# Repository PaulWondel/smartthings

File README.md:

# THIS PROJECT HAS BEEN FINALIZED AND SHELVED

# Minor Smart Things

This github is for all the files I create or save during the minor `Smart Things` that I
follow at the [Rotterdam University of Applied Sciences](https://rotterdamuas.com/) - Applied Computer Science
([Hogeschool Rotterdam](https://www.hogeschoolrotterdam.nl/) - Technische Informatica).

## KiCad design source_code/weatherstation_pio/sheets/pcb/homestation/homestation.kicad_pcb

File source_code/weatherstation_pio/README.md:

# Weather Station with ESP8266

## Libraries
Required library from RicArch97: https://github.com/RicArch97/ESP-smart-things.

## Important note
To use the ssid and password you will need to create your own `credentials.h` headerfile using
the `credentials_example.h`. You can simply just copy it.  
To upload the data to your own website edit the information in the `httpclient.h` file.

## Design
Here are the designs on how the circuit and system is built.

### Fritzing

### Electrical Scheme

### Software Architecture

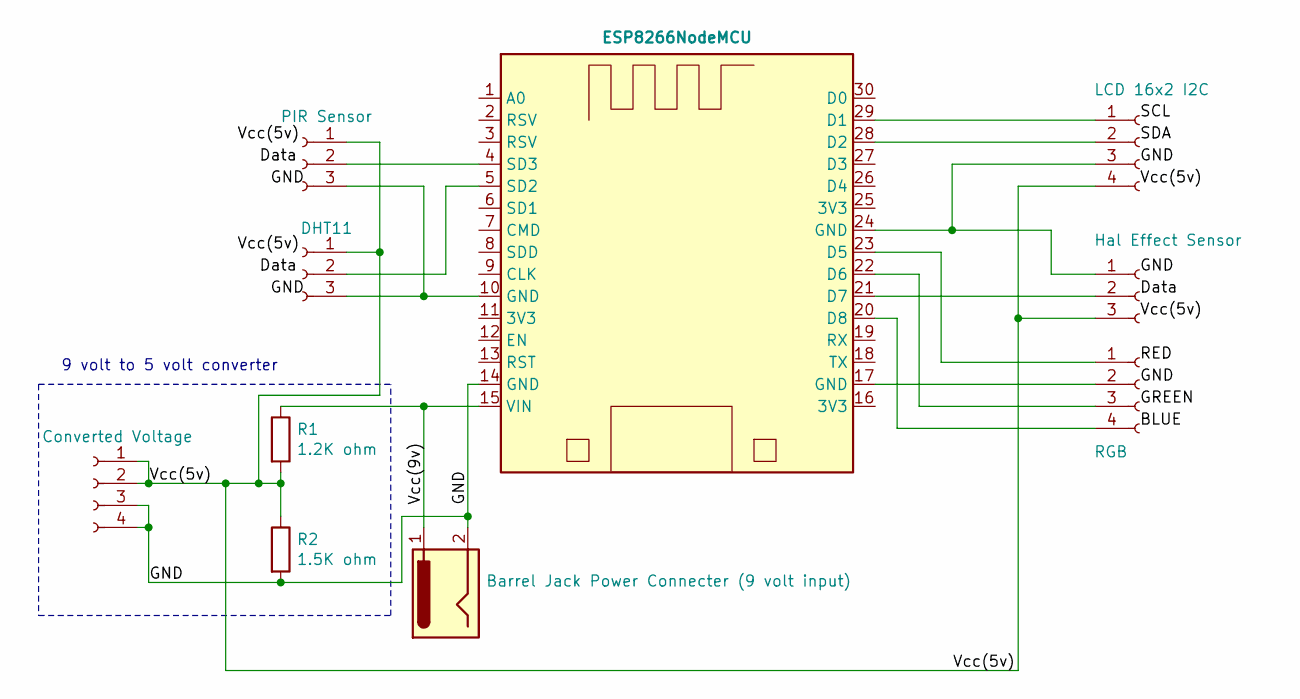
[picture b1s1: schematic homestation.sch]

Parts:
J1: Converted Voltage; PinHeader_1x04_P2.54mm_Vertical
J2: PIR Sensor; PinHeader_1x03_P2.54mm_Vertical
J3: DHT11; PinHeader_1x03_P2.54mm_Vertical
J4: Barrel Jack Power Connecter (9 volt input); BarrelJack_Horizontal
J5: LCD 16x2 I2C; PinHeader_1x04_P2.54mm_Vertical
J6: Hal Effect Sensor; PinHeader_1x03_P2.54mm_Vertical
J7: RGB; PinHeader_1x04_P2.54mm_Vertical
R1: 1.2K ohm; R_Axial_DIN0204_L3.6mm_D1.6mm_P7.62mm_Horizontal
R2: 1.5K ohm; R_Axial_DIN0204_L3.6mm_D1.6mm_P7.62mm_Horizontal
U1: ESP8266NodeMCU; ESP8266_nodeMCU_V1

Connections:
/GND: J1.3, J1.4, J4.2, R2.2, U1.14 (GND)
/Vcc(5v): J1.1, J1.2, J2.1, J3.1, J5.4, J6.3, R1.2, R2.1
/Vcc(9v): J4.1, R1.1, U1.15 (VIN)
unnamed: J2.2, U1.4 (SD3)
unnamed: J2.3, J3.3, U1.10 (GND)
unnamed: J3.2, U1.5 (SD2)
unnamed: J5.1, U1.29 (D1)
unnamed: J5.2, U1.28 (D2)
unnamed: J5.3, J6.1, U1.24 (GND)
unnamed: J6.2, U1.21 (D7)
unnamed: J7.1, U1.23 (D5)
unnamed: J7.2, U1.17 (GND)
unnamed: J7.3, U1.22 (D6)
unnamed: J7.4, U1.20 (D8)

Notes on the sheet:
9 volt to 5 volt converter

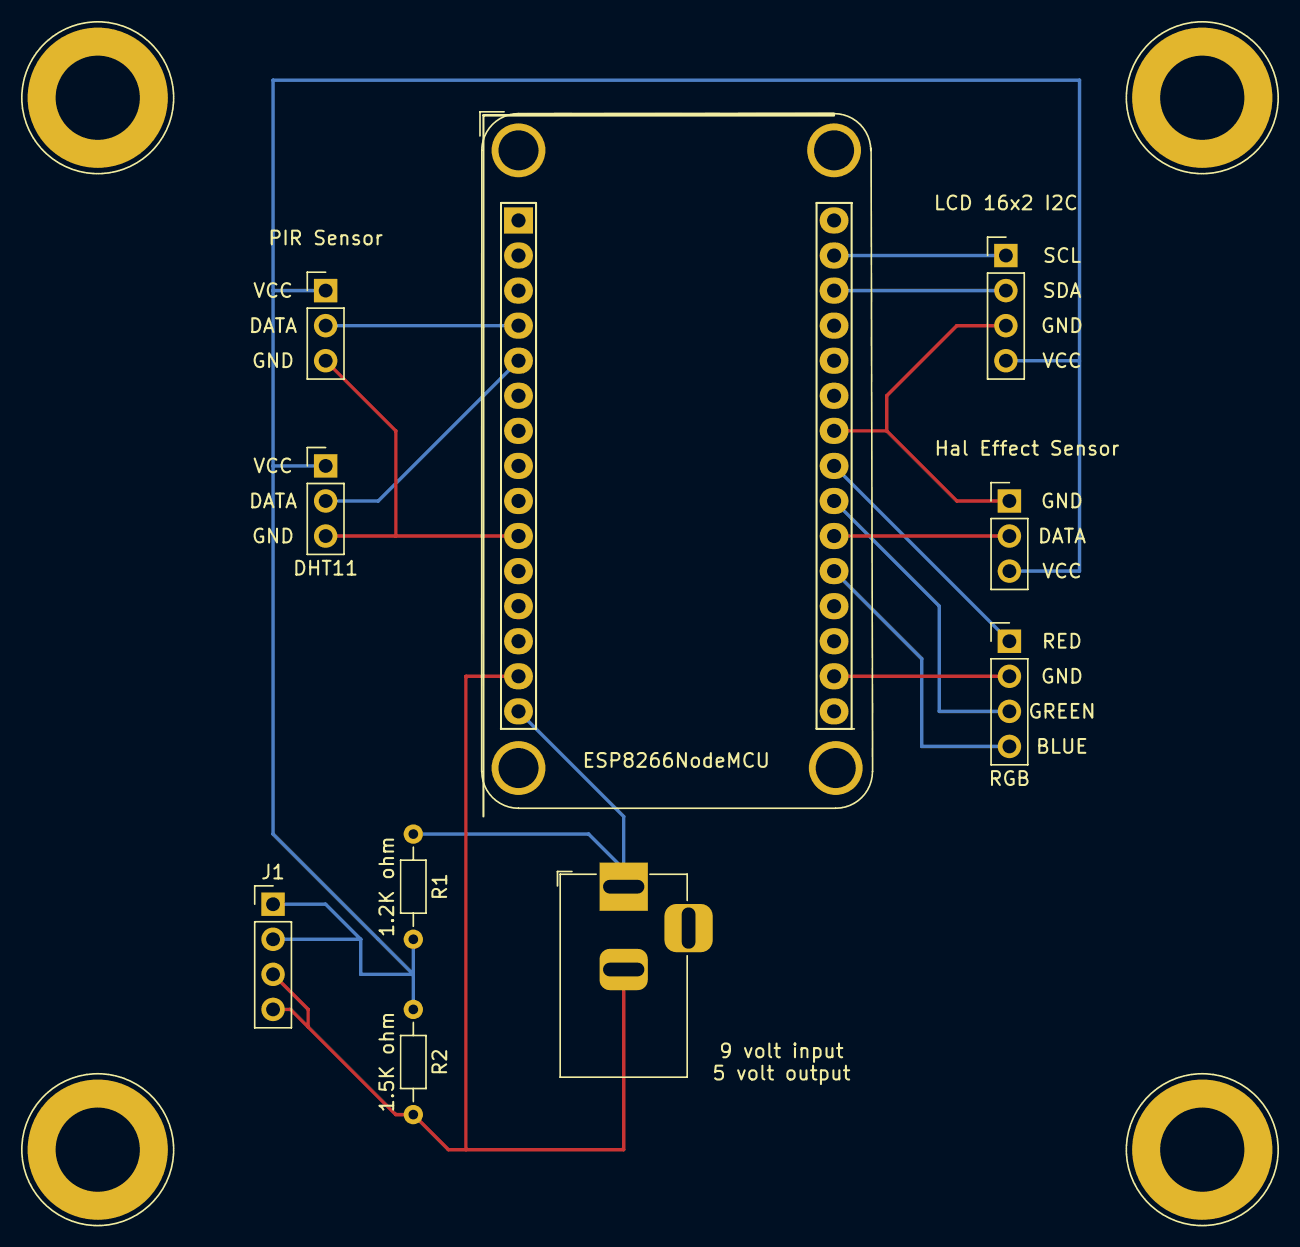
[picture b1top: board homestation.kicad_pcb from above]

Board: 2 copper layers, 10 parts (0 on the bottom side), 14 nets.

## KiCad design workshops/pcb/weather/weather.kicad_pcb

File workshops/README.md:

# README
This directory contains the documents and codes that are used during the friday practical workshops.

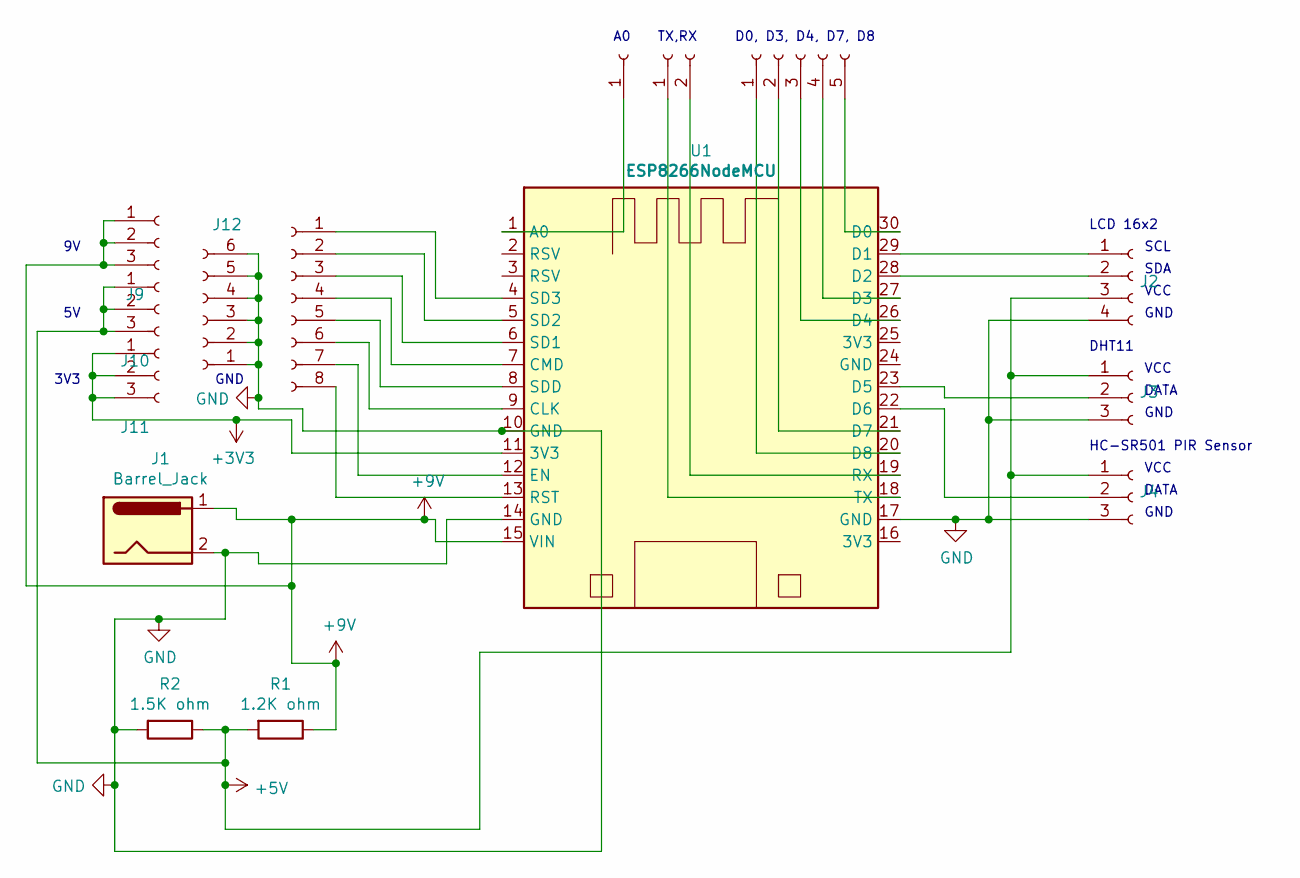
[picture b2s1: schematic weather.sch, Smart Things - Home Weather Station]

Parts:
J1: Barrel_Jack; BarrelJack_Horizontal
J2: Conn_01x04_Female; PinHeader_1x04_P2.54mm_Vertical
J3, J4, J9, J10, J11: Conn_01x03_Female; PinHeader_1x03_P2.54mm_Vertical
J5: Conn_01x08_Female; PinHeader_1x08_P2.54mm_Vertical
J6: Conn_01x01_Female; PinHeader_1x01_P2.54mm_Vertical
J7: Conn_01x02_Female; PinHeader_1x02_P2.54mm_Vertical
J8: Conn_01x05_Female; PinHeader_1x05_P2.54mm_Vertical
J12: Conn_01x06_Female; PinHeader_1x06_P2.54mm_Vertical
R1: 1.2K ohm; R_Axial_DIN0309_L9.0mm_D3.2mm_P12.70mm_Horizontal
R2: 1.5K ohm; R_Axial_DIN0309_L9.0mm_D3.2mm_P12.70mm_Horizontal
U1: ESP8266NodeMCU; ESP8266_nodeMCU_V1

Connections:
+3V3: J11.1, J11.2, J11.3, U1.11 (3V3)
+5V: J2.3, J3.1, J4.1, J10.1, J10.2, J10.3, R1.2, R2.1
+9V: J1.1, J9.1, J9.2, J9.3, R1.1, U1.15 (VIN)
GND: J1.2, J2.4, J3.3, J4.3, J12.1, J12.2, J12.3, J12.4, J12.5, J12.6, R2.2, U1.10 (GND), U1.14 (GND), U1.17 (GND)
unnamed: J2.1, U1.29 (D1)
unnamed: J2.2, U1.28 (D2)
unnamed: J3.2, U1.23 (D5)
unnamed: J4.2, U1.22 (D6)
unnamed: J5.1, U1.4 (SD3)
unnamed: J5.2, U1.5 (SD2)
unnamed: J5.3, U1.6 (SD1)
unnamed: J5.4, U1.7 (CMD)
unnamed: J5.5, U1.8 (SDD)
unnamed: J5.6, U1.9 (CLK)
unnamed: J5.7, U1.12 (EN)
unnamed: J5.8, U1.13 (RST)
unnamed: J6.1, U1.1 (A0)
unnamed: J7.1, U1.18 (TX)
unnamed: J7.2, U1.19 (RX)
unnamed: J8.1, U1.20 (D8)
unnamed: J8.2, U1.21 (D7)
unnamed: J8.3, U1.26 (D4)
unnamed: J8.4, U1.27 (D3)
unnamed: J8.5, U1.30 (D0)

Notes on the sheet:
LCD 16x2
DHT11
SCL
SDA
VCC
GND
DATA
HC-SR501 PIR Sensor
D0, D3, D4, D7, D8
TX,RX
3V3

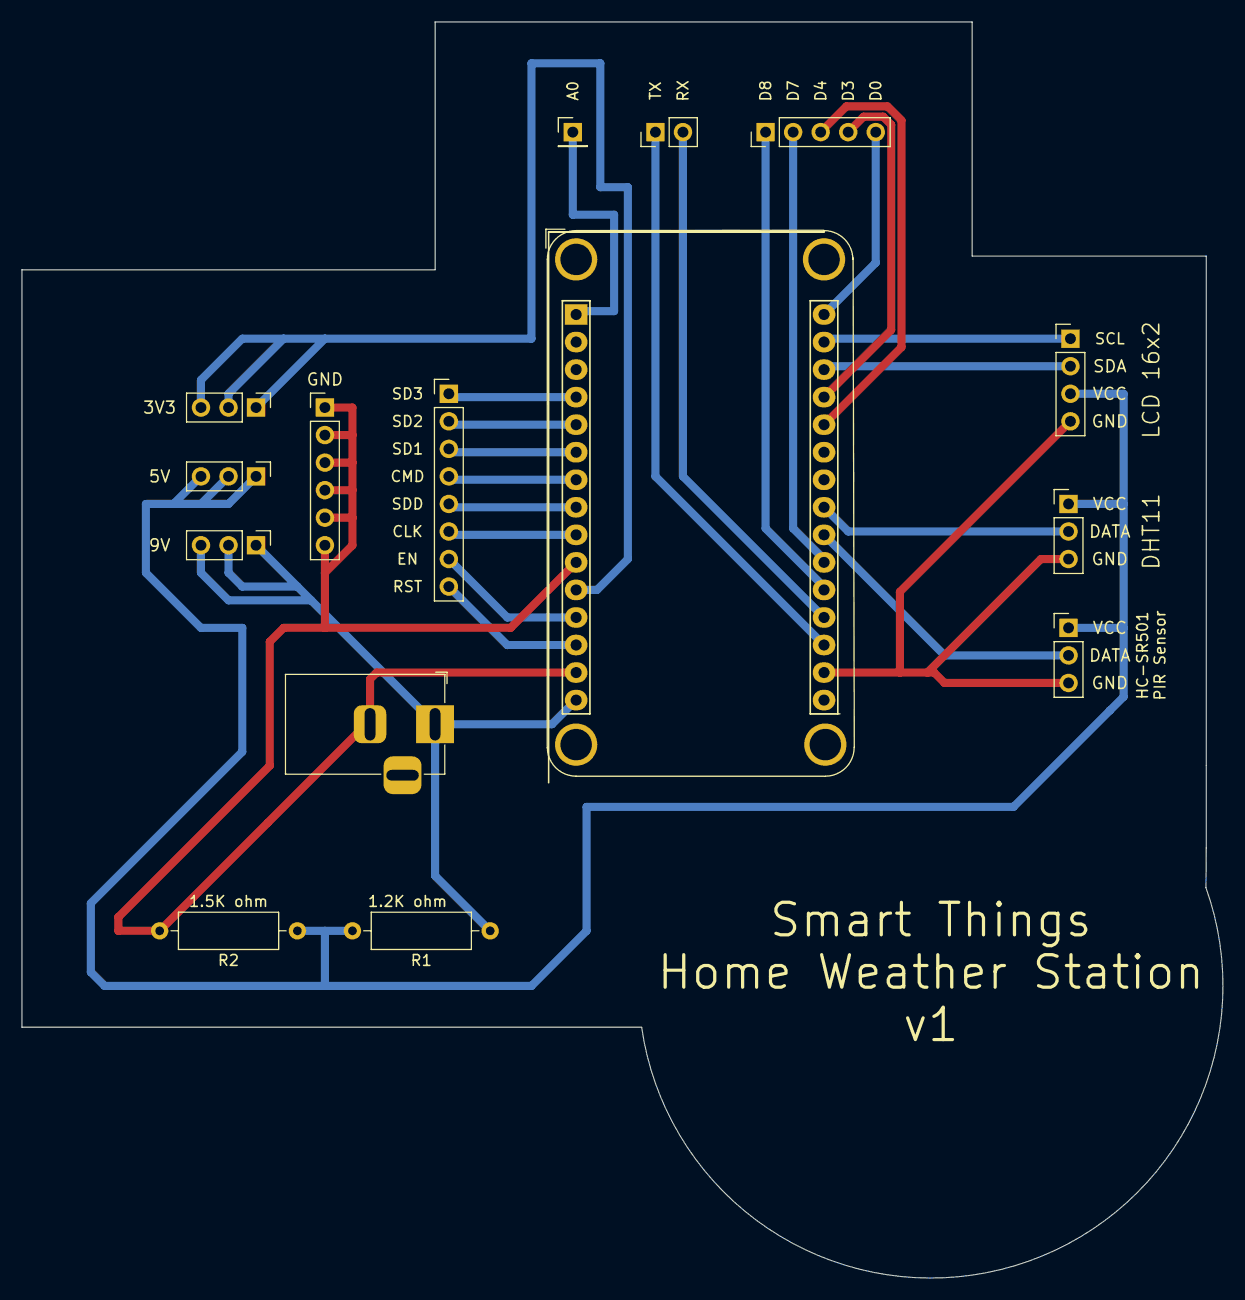
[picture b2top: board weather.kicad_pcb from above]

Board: 2 copper layers, 110.8 x 115.8 mm, 15 parts (0 on the bottom side), 24 nets.

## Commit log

2020-09-10 Update cursushandleiding.pdf, dragon-quest-logo.png, and 4 more files...
2020-09-10 Update README.md, dragon-quest-logo.png, and 5 more files...
    - Added LED test file
2020-09-10 Update lcd_test.ino
    - problem with LCD display ST7920 128x64 working with ESP8266
    - Serial now showing on LCD display
2020-09-13 Update ST7920_DHT22.ino, lcd_test.ino, and 3 more files...
    - LCD 16x2 with esp8266
    - LCD 128x64 with arduino uno
    - edited box graphics
2020-09-13 Update weather.ino
    - Connection from esp to website failed.
2020-09-13 Update weather.ino
    - ziggo port blocked, can't send data to website from esp
2020-09-13 Update Boxes.eps, Snap_Flex_Box_with_Initials.svg, and 6 more files...
2020-09-15 Update httpclient.ino, extra.h, and 5 more files...
2020-09-15 Update weather.ino
    Fixed upload error to website.
2020-09-16 Update .gitignore, httpclient.ino, and 3 more files...
    - Sorted functions into header files
    - Created password file with headerfile
2020-09-23 Update lcd.h and weather.ino
    - circuit fixed
    - added motion sensor
    - LCD turns off if not used
2020-09-24 Update weather.ino
    - added 2 second delay after detecting motion
2020-09-24 Update hcsr04.ino, dragon-quest-logo.png, and 4 more files...
    - deleted unused files
2020-09-24 Update .gitignore, Project.xml, and 39 more files...
2020-09-28 added workshop machinelearning files
2020-09-28 Update:
    + coverted project from arduino ide to platformio
    + added SmartThingsESP8266 library from RicArch97
2020-09-29 Update
    + fixed local http server on esp8266, ip now accessable
    + added links to other websites on hosted website
    + API implementation completed
    + edited local http/html server website
    + updates values online every 10 minutes
2020-09-29 changed humidity from float to int
2020-09-30 new lasercut designs
2020-09-30 quick update
2020-10-02 Update:
    [x] Added new header files
    [x] Cleaned up main source code file
    [] Anemometer functions need to be added
2020-10-02 edited readme files
2020-10-02 Update README.md, circuit.fzz, and 2 more files...
2020-10-02 Update README.md, architecture.drawio, and 2 more files...
2020-10-02 Update credentials_example.h, httpclient.h, and 5 more files...
2020-10-02 Update Birds House.stl, anemometr_v_2.stl, and 167 more files...
2020-10-02 Update:
    - Sorted and moved files in directories according for easy navigation
    - Added readme files in directories
2020-10-06 Update:
    - Replaced IR sensor with PIR sensor
    - Display reactions to motion instead of distance
2020-10-08 Update README.md, axe_haut.STL, and 4 more files...
2020-10-14 removed .vscode/
2020-10-14 updated gitignore
2020-10-14 Update circuit.fzz, circuit_bb.png, and 14 more files...
2020-10-14 Update ESP8266_nodeMCU_V1.kicad_mod, MCU_Espressiv_8266nodemcu.lib, and 9 more files...
    - Must add a 9v to 5v converters for sensors and LCD display that take 5v
2020-10-15 Update custom_logo.kicad_mod, fp-info-cache, and 7 more files...
2020-10-16 Update fp-info-cache
2020-10-27 Update sensors.h and weatherstation.cpp
    - Added windspeed sensor with interrupt method.
2020-10-27 Updated files:
    - weatherstation.cpp: added speed detect method
    - sensors.h: added method to calculate rpm and mps from windPin
    - lcd.h: added method to display windspeed value
    - webserver: added variable to send windspeed value to website
2020-11-09 Update:
    - Fixed calculation of RPM and MPS
2020-11-10 modification in weatherstation.cpp
2020-11-11 Freed pwm pins for RGB led, changed dht, prox pins
2020-11-11 Update:
    - Added RGB functions
    - New sphere headerfile
2020-11-14 Update architecture.drawio, architecture.png, and 10 more files...
2020-11-14 Update _autosave-homestation.sch, homestation-cache.lib, and 2 more files...
2020-11-14 Removed unnessesary comments
2020-11-15 Home station finalized and report finalized.
2020-11-15 PROJECT FINALIZED AND SHELVED
    Files set for Arduino IDE
2020-11-16 fixed incorrect pins
